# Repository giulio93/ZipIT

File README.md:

ZipIT
=====

ZipIT is a simple anti-theft device to be installed on bag,suitcase or luggage based on Arduino.
When the thief opens your zip, the device sends an warning to your smartphone through bluetooth.

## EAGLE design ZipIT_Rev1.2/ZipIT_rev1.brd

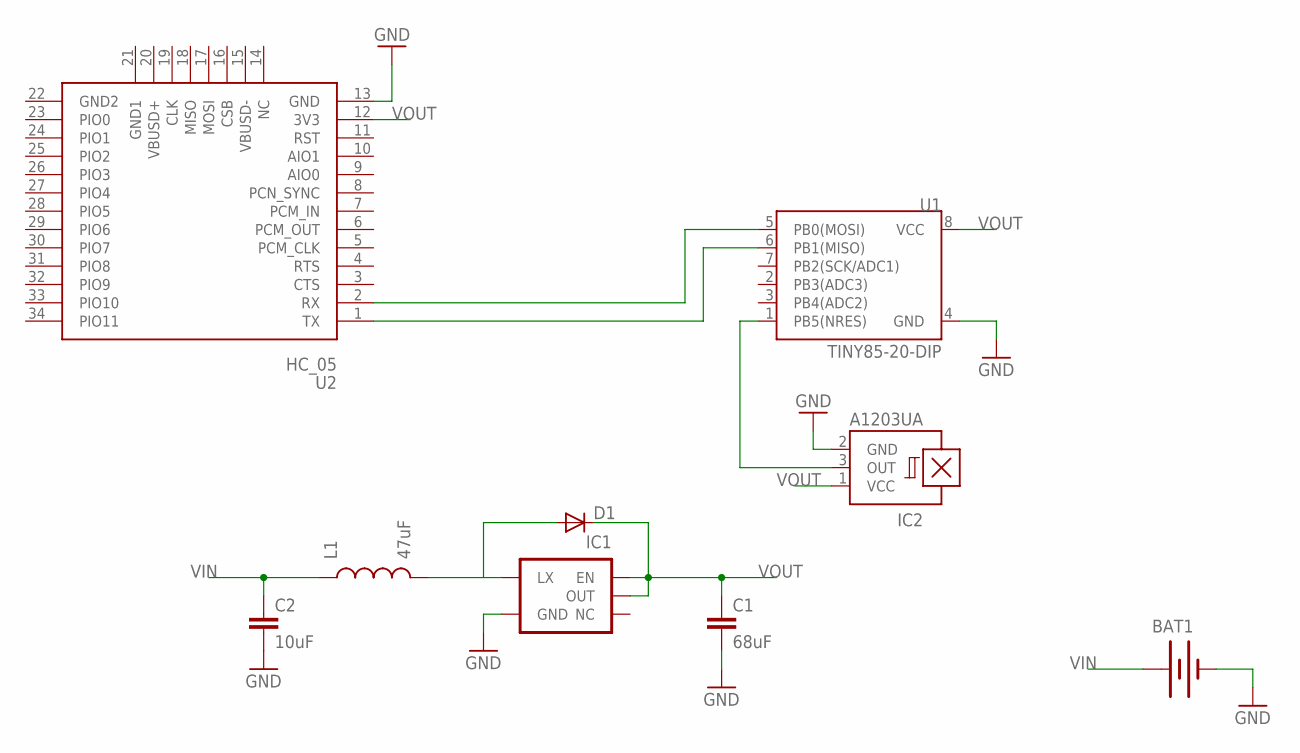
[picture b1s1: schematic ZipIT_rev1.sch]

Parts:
BAT1: BATTERYAAA; BATTERY-AAA
C1: 68uF; C1210
C2: 10uF; C1206
D1: DIODE-DO214AC; DO214AC
IC1: V_REG_NCP1400SOT23-5; SOT23-5
IC2: A1203UA; SIP3-UA
L1: 47uF; CR54
U1: TINY85-20-DIP; DIP08
U2: HC_05; BLUETOOTH_SMD

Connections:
GND: BAT1.GND@1 (-), C1.2, C2.2, IC1.4 (GND), IC2.2 (GND), U1.4 (GND), U2.13 (GND)
unnamed: D1.A, IC1.5 (LX), L1.P$2 (2)
unnamed: IC2.3 (OUT), U1.1 (PB5(NRES))
unnamed: U1.6 (PB1(MISO)), U2.1 (TX)
unnamed: U1.5 (PB0(MOSI)), U2.2 (RX)
VIN: BAT1.PWR@1 (+), C2.1, L1.P$1 (1)
VOUT: C1.1, D1.C, IC1.1 (EN), IC1.2 (OUT), IC2.1 (VCC), U1.8 (VCC), U2.12 (3V3)

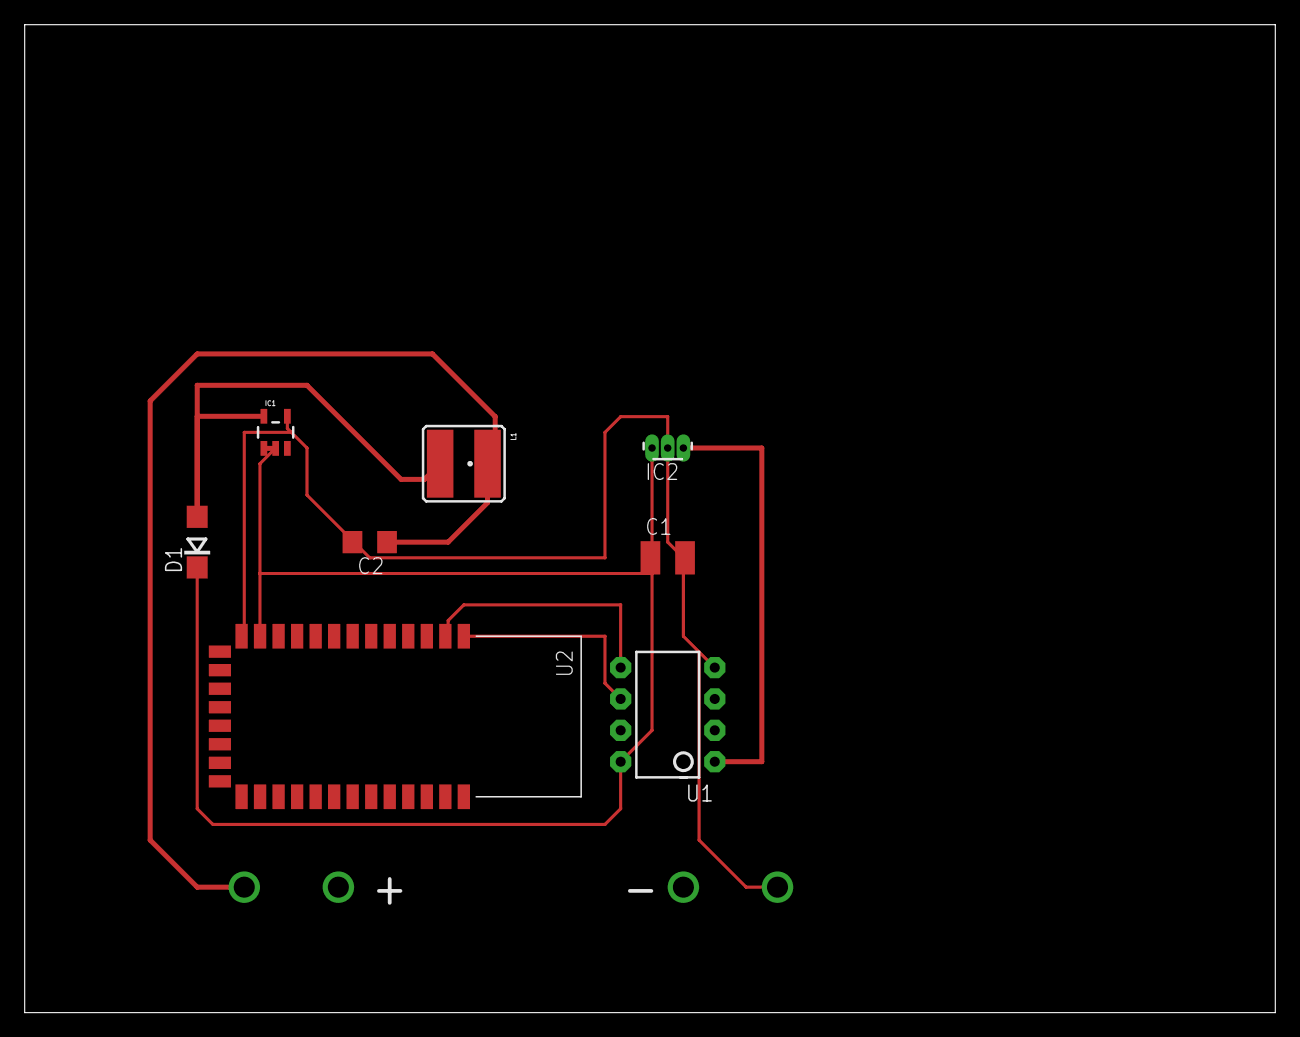
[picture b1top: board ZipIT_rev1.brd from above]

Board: 2 copper layers, 101.3 x 80.0 mm, 9 parts (0 on the bottom side), 7 nets.

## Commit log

2013-06-30 Update: Arduino_code
2013-06-30 Update :Android App
2013-09-25 Done
    new disposition
2013-09-26 Same .sch other .brd
2014-03-30 Apk
    Android App
2014-03-30 Delete
2014-03-31 Upload source code app
2014-05-06 Update README.md
    New

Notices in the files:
parts and their libraries:
SparkFun-PowerIC: Licensing: CC v3.0 Share-Alike You are welcome to use this library for commercial purposes.
